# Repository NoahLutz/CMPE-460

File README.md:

# CMPE-460
Interface and Digital Electronics

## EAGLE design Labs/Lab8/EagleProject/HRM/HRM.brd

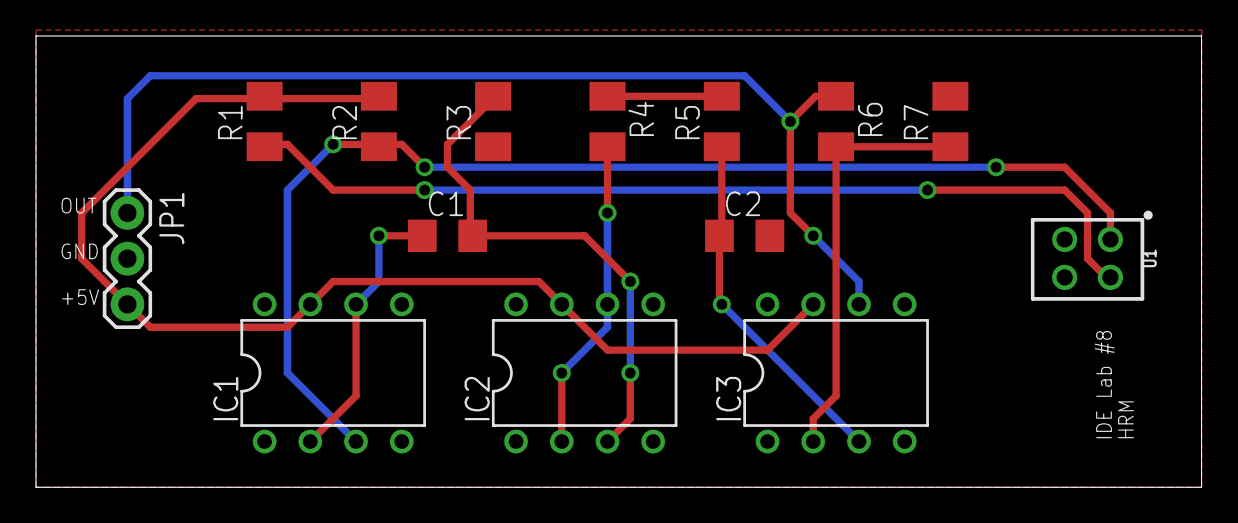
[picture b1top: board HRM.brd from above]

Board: 2 copper layers, 64.8 x 25.1 mm, 14 parts (0 on the bottom side), 11 nets.

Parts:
C1: 3.48uF; C3216
C2: 1uF; C3216
IC1, IC2, IC3: UA741P; DIL08
JP1: 1X03
R1: 65; M1206
R2: 10k; M1206
R3: 57.3k; M1206
R4: 8.1k; M1206
R5: 8.14k; M1206
R6: 98k; M1206
R7: 0.981k; M1206
U1: QRD1114

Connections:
+5V: IC1.7, IC2.7, IC3.7, JP1.3, R1.2, R2.2
GND: C2.2, IC1.4, IC2.4, IC3.4, JP1.2, R3.1, R7.2, U1.2, U1.3
unnamed: R1.1, U1.4
unnamed: IC1.3, R2.1, U1.1
unnamed: IC2.2, IC2.6, R4.2
unnamed: C1.1, IC1.2, IC1.6
unnamed: C1.2, IC2.3, R3.2
unnamed: R4.1, R5.2
unnamed: C2.1, IC3.3, R5.1
unnamed: IC3.2, R6.2, R7.1
OUT: IC3.6, JP1.1, R6.1

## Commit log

2019-09-05 added completed lab1 source files
2019-09-05 added K64F manual
2019-09-05 added reports folder
2019-09-06 added gitignore
2019-09-06 removed gitignored files
2019-09-06 added lab manual pdf
2019-09-06 updated lab1 files
2019-09-06 added table PDF
2019-09-06 added lab2 source files
2019-09-17 added lab2 files and report
2019-09-17 added template LaTeX report and beginning of lab3 report
2019-09-19 [WIP] update for report 3
2019-09-19 final version of lab 3 report
2019-09-19 added homework directory
2019-09-19 fixed spelling errors in lab3
2019-10-07 code and report update
2019-11-06 udpated labs and report folders
2019-11-06 added initial project files
2019-11-06 refactoring for final proj
2019-11-06 not sure what I changed hope it works
2019-11-06 hope it works maybe
2019-11-07 updated final project, might be ready to test
2019-11-07 added unneeded files to .gitignore
2019-11-07 removed ignored files
2019-11-10 udpated gitignore again
2019-11-10 added area calculation for area under signal
2019-11-10 added function for detecting edges/color content
2019-11-11 added uart.c/h from lab4
2019-11-11 added initialization code for uart0 and uart 3
2019-11-12 added eagle project
2019-11-13 update from work in NXP lab
2019-11-13 push from laptop
2019-11-13 update from NXP
2019-11-13 PID Implementation
2019-11-14 added HRM scope caputre
2019-11-14 set sampling frequency to 33Hz
2019-11-14 added pspice bode plot
2019-11-14 updated bode plot with points
2019-11-14 Lab Report
    Highlighted areas are left to be completed.
    and transfer functions?
2019-11-14 Uart
    Bluetooth works!
2019-11-14 Fixed compilation errors due to merge
2019-11-14 Figure 8 working :smile:
2019-11-18 [WIP] update from noah's desktop
2019-11-19 [WIP] update of queue files
2019-11-19 got uart via BT working, jesus why was that so difficult
2019-11-19 added debug prints
2019-11-19 added stub for calibrating thresholds
2019-11-19 added queue files to keil project
2019-11-19 broke everything somehow
2019-11-20 added threshold enum and structs
2019-11-20 added some state logic for calibration
2019-11-20 filled out calibration stub and added helper functions for calibration
2019-11-20 fixed logic error where if cal is bad/no cal
2019-11-21 should now assume edge is at end of camera data if no edge is found
2019-11-21 we can turn in circles :D
2019-11-22 added motor state machine stuff
2019-11-22 got PID somewhat tuned, still needs speed variation
2019-12-05 added simpified schematic
2019-12-05 Report Photos

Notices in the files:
parts and their libraries:
SparkFun-Sensors: Licensing: Creative Commons ShareAlike 4.0 International - https://creativecommons.org/licenses/by-sa/4.0
